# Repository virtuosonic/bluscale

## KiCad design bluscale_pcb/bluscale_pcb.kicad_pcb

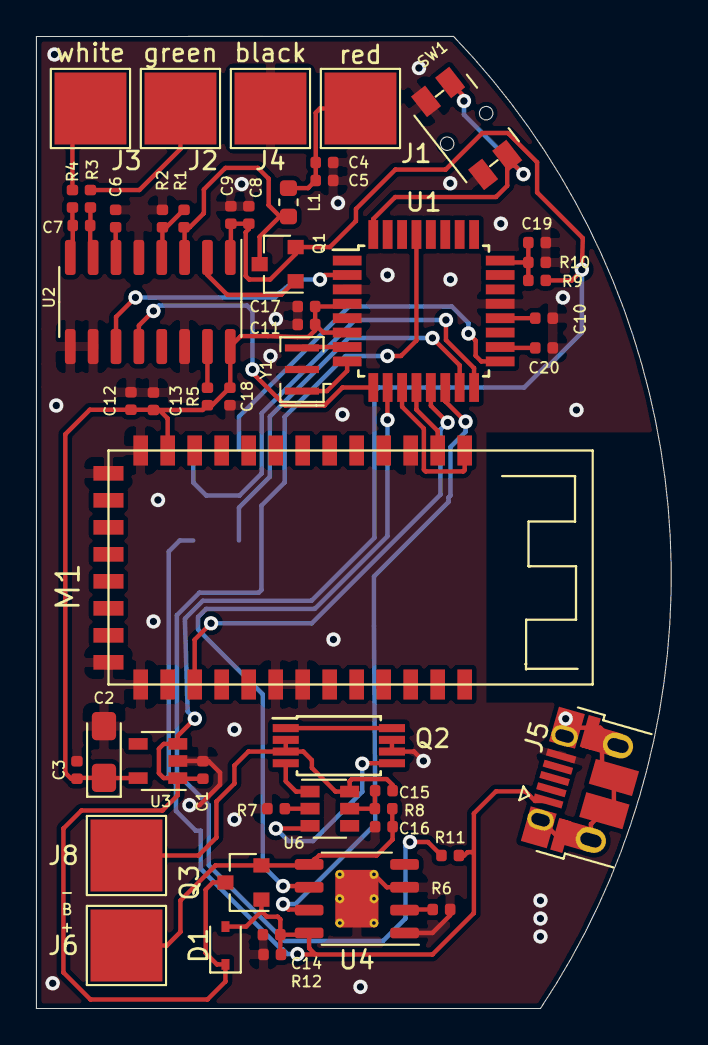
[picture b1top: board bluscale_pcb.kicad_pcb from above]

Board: 2 copper layers, 35.3 x 54.0 mm, 53 parts (1 on the bottom side), 39 nets.

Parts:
C1, C5, C9, C12, C16, C17: 10uF 6.3V; C_0402_1005Metric
C2: 10uF 6.3V; CP_EIA-3216-10_Kemet-I_Pad1.58x1.35mm_HandSolder
C3, C4, C6, C7, C8, C10, C11, C13, C14, C15, C18, C19, C20: .1uF 6.3V; C_0402_1005Metric
D1: BAT54HT1G; D_SOD-323
J1, J6: red; TestPoint_Pad_4.0x4.0mm
J2: green; TestPoint_Pad_4.0x4.0mm
J3: white; TestPoint_Pad_4.0x4.0mm
J4, J8: black; TestPoint_Pad_4.0x4.0mm
J5: USB_B_Micro; USB_Micro-B_Amphenol_10103594-0001LF_Horizontal
J7: Conn_02x03_Odd_Even; PinHeader_2x03_P2.54mm_Vertical_SMD
L1: 3.3uH 15mA 1.55ohms; L_0603_1608Metric
M1: HM-10S-B; BLE-HM-10
Q1: MMBT4403; SOT-23
Q2: FS8205A; TSSOP-8_4.4x3mm_P0.65mm
Q3: FDN340P; SOT-23
R1: 20k; R_0402_1005Metric
R2: 8.2k; R_0402_1005Metric
R3, R4, R8: 100ohms; R_0402_1005Metric
R5, R11, R12: 10k; R_0402_1005Metric
R6: 1.2k; R_0402_1005Metric
R7: 1k; R_0402_1005Metric
R9: 10M; R_0402_1005Metric
R10: 3M48; R_0402_1005Metric
SW1: EVQ-PUM02K; Panasonic_EVQPUM_EVQPUD
U1: ATmega328P-AU; TQFP-32_7x7mm_P0.8mm
U2: HX711; SOIC-16_3.9x9.9mm_P1.27mm
U3: MIC5205-2.8YM5; SOT-23-5
U4: TP4056-42-SOP8-PP; HTSOP-8-1EP_3.9x4.9mm_P1.27mm_EP2.4x3.2mm_ThermalVias
U6: DW01A; SOT-23-6
Y1: CSTNE8M00G550000R0; Resonator_SMD_muRata_CSTxExxV-3Pin_3.0x1.1mm

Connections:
+2V8: C2.1, C3.1, C11.1, C12.1, C13.1, C17.2, C18.2, M1.3.3V, R5.1, U1.4, U1.6, U2.16, U3.5
+3V8: C1.1, C8.2, C9.2, D1.1, Q1.2, Q3.3, R9.1, U2.1, U3.1, U3.3
+5V: C14.1, D1.2, J5.1, J7.2, Q3.1, R11.1, R12.1, U4.8
+BATT: C16.2, J6.1, Q3.2, R8.1, U4.5
-BATT: C15.1, J8.1, Q2.2, Q2.3, U6.6
/A1: C19.2, R9.2, R10.1, U1.24
/D6: U1.10, U4.6
/D7: M1.UART_TX, U1.11
/D8: M1.UART_RX, U1.12
/D9: M1.PIO1, U1.13
/D10: U1.14, U4.7
/D11: J7.4, U1.15
/D12: J7.1, U1.16
/D13: J7.3, U1.17
/RESET: J7.5, R11.2, U1.29
/XTAL2: U1.8, Y1.1
/hx711clk: U1.2, U2.11
/hx711out: U1.9, U2.12
GND: C1.2, C2.2, C3.2, C4.2, C5.2, C6.1, C8.1, C9.1, C10.2, C11.2, C12.2, C13.2, C14.2, C16.1, C17.1, C18.1, C19.1, C20.2, J4.1, J5.5, J7.6, M1.GND1, M1.GND2, M1.GND3, M1.GND4, M1.PIO4, M1.PIO5, M1.UART_CTS, Q2.6, Q2.7, R2.2, R6.2, R7.2, R10.2, R12.2, SW1.2, U1.3, U1.5, U1.21, U2.5, U2.9, U2.10, U2.14, U3.2, U4.1, U4.3, U4.9, Y1.2
unnamed: C4.1, C5.1, J1.1, L1.1
unnamed: C6.2, U2.6
unnamed: C7.1, R3.1, U2.7
unnamed: C7.2, R4.1, U2.8
unnamed: C10.1, U1.20
unnamed: C15.2, R8.2, U6.5
unnamed: C20.1, U1.18
unnamed: J2.1, R3.2
unnamed: J3.1, R4.2
unnamed: L1.2, Q1.3, R1.2, U2.3
unnamed: Q1.1, U2.2
unnamed: Q2.1, Q2.8
unnamed: Q2.4, U6.1
unnamed: Q2.5, U6.3
unnamed: R1.1, R2.1, U2.4
unnamed: R5.2, U2.15
unnamed: R6.1, U4.2
unnamed: R7.1, U6.2
unnamed: SW1.1, U1.32
unnamed: U1.7, Y1.3

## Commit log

2023-09-13 arduino project
2023-09-13 specs and fritzing file
2023-09-13 qtquick app project
2023-09-13 kicad project
